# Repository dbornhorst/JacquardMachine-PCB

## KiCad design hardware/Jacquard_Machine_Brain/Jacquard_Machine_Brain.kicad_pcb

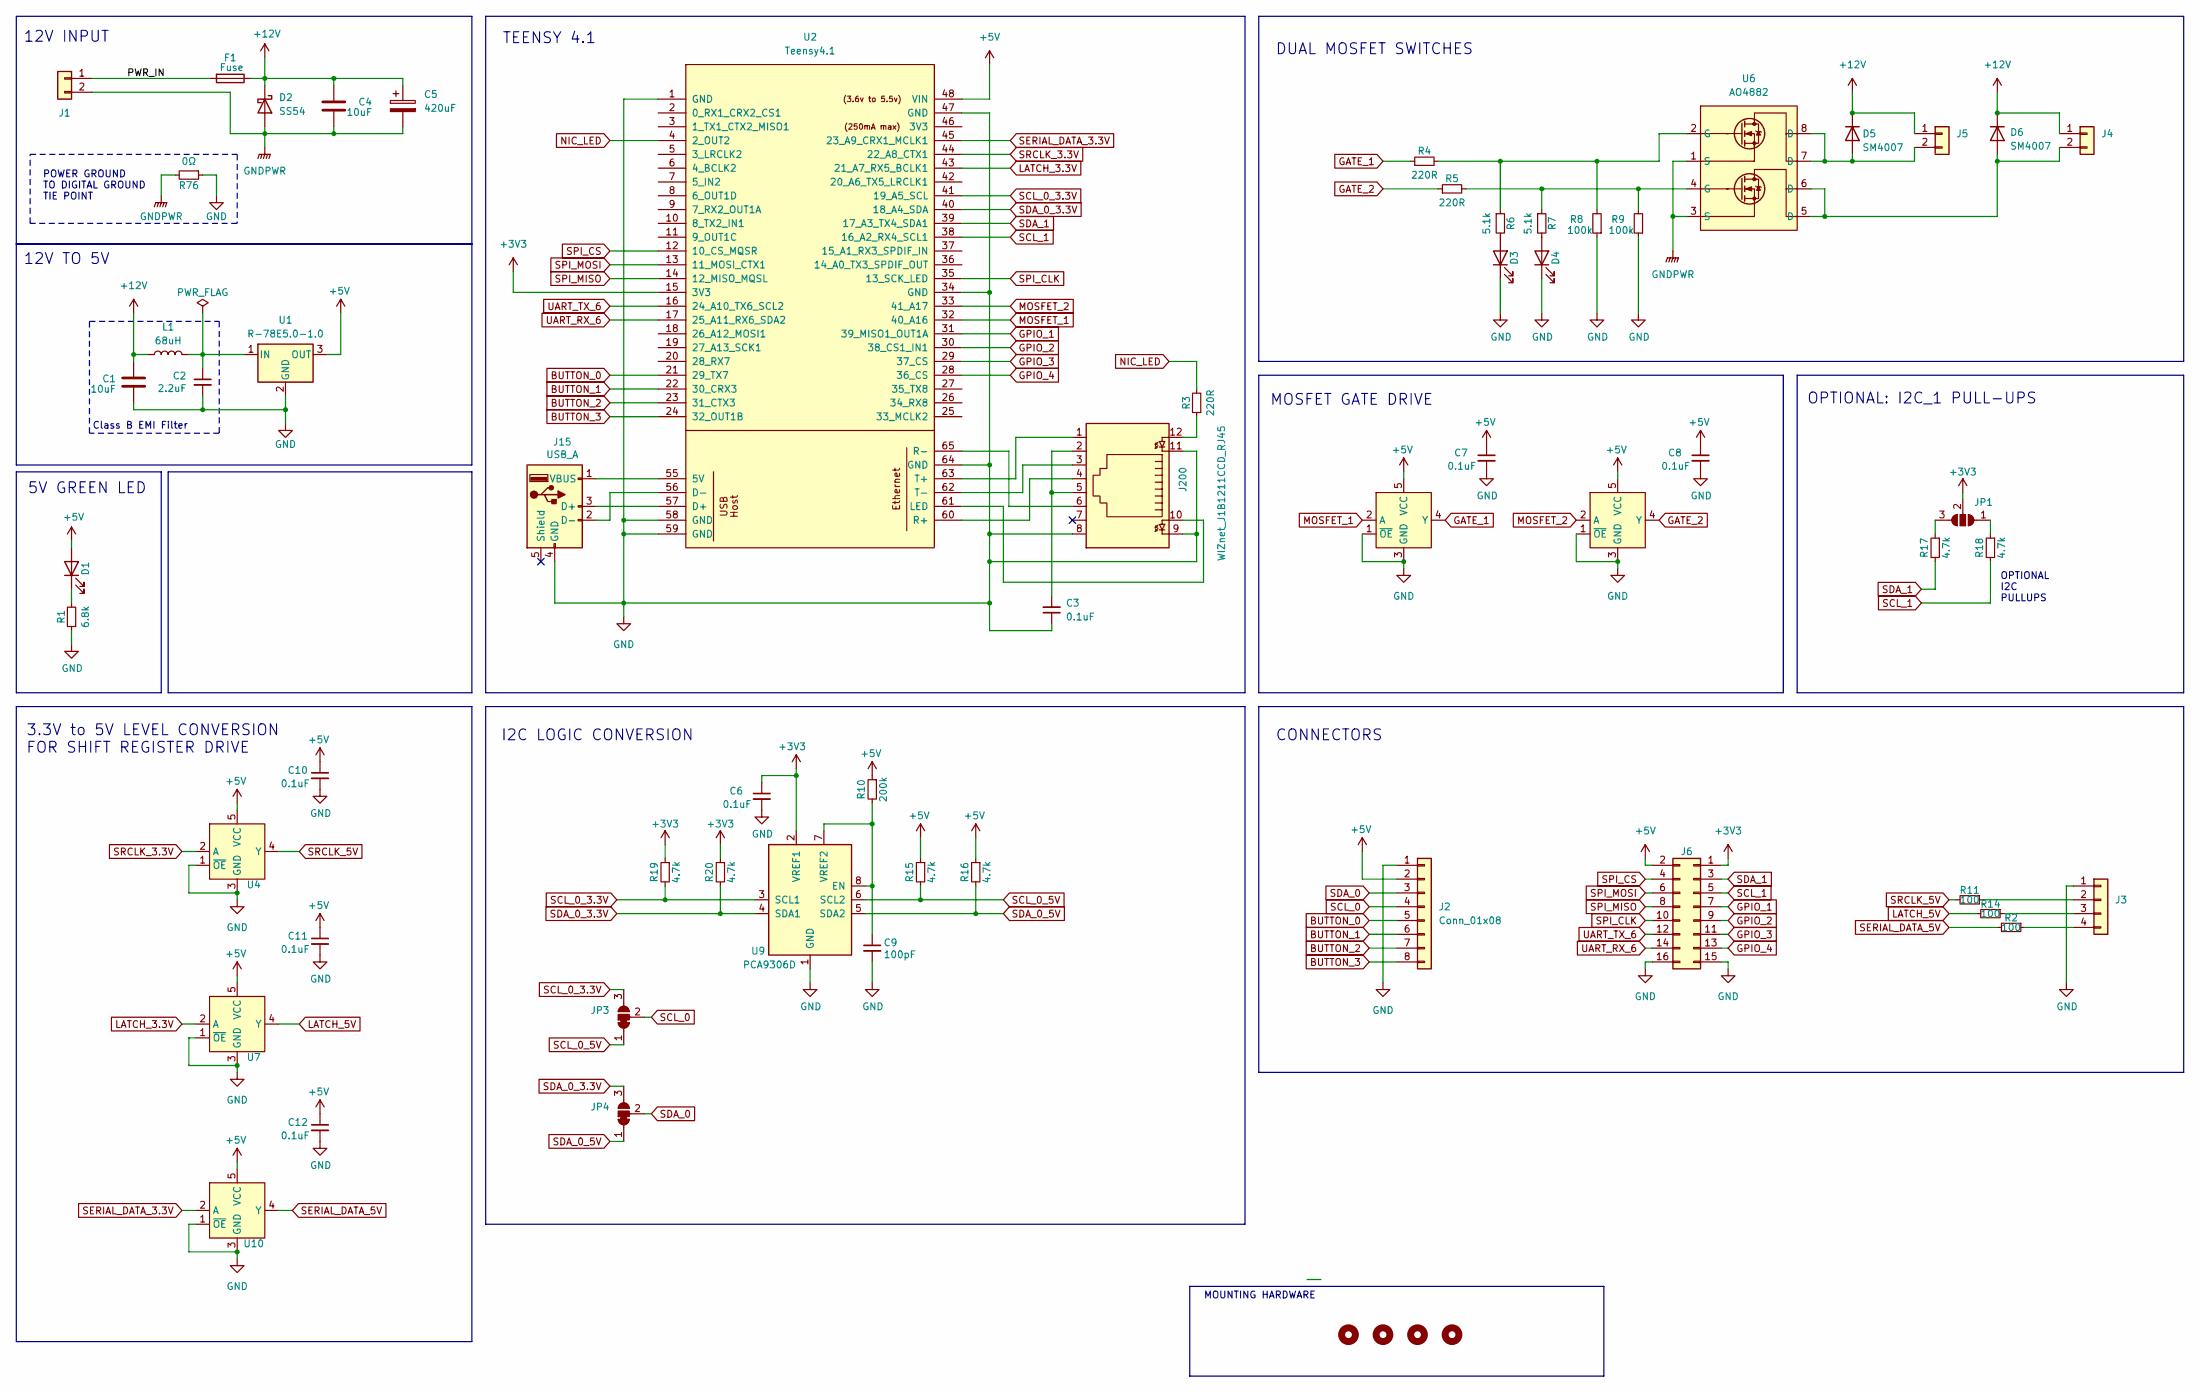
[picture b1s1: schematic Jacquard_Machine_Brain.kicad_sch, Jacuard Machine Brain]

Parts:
C1, C4: 10uF; C_1206_3216Metric; LCSC C13585
C2: 2.2uF; C_0805_2012Metric; LCSC C377773
C3: 0.1uF; C_0805_2012Metric; LCSC C49678
C5: 420uF; CP_Elec_10x7.9; LCSC C3350
C6, C7, C8, C10, C11, C12: 0.1uF; C_0402_1005Metric; LCSC C1525
C9: 100pF; C_0402_1005Metric; LCSC C1546
D1: GREEN LED; LED_0805_2012Metric; LCSC C2297
D2: SS54; D_SMA; LCSC C22452
D3, D4: RED LED; LED_0402_1005Metric; LCSC C397045
D5, D6: SM4007; D_SOD-123; LCSC C64898
F1: Fuse; Fuseholder_2AG_5x15mm_Littelfuse_01110501Z; LCSC C151075
H1, H2, H3, H4: MountingHole; MountingHole_3.2mm_M3_Pad_Via
J1: Terminal Block; TerminalBlock_Phoenix_MKDS-1-2-3.81_1x02_P3.81mm_Horizontal; LCSC C89123
J2: Conn_01x08; PinSocket_1x08_P2.54mm_Vertical; LCSC C42431840
J3: JST-SH 01x04; JST_SH_BM04B-SRSS-TB_1x04-1MP_P1.00mm_Vertical; LCSC C160390
J4, J5: Conn_01x02; PinSocket_1x02_P2.54mm_Vertical; LCSC C7499322
J6: Conn_02x08_Odd_Even; PinSocket_2x08_P2.54mm_Vertical; LCSC C30734
J15: USB_A; SAMTEC_USB-A-S-S-W-TH; LCSC C5815125
J200: WIZnet_J1B1211CCD_RJ45; Digikey P/N 1278-1052-ND
JP1: SolderJumper_3_Bridged123; SolderJumper-3_P1.3mm_Open_RoundedPad1.0x1.5mm
JP3, JP4: SolderJumper_3_Bridged12; SolderJumper-3_P1.3mm_Bridged12_RoundedPad1.0x1.5mm_NumberL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
L1: 68uH; L_Sunlord_SWPA6045S; LCSC C53663
R1: 6.8k; R_0603_1608Metric; LCSC C23212
R2, R11, R14: 100; R_0402_1005Metric; LCSC C25076
R3: 220R; R_0805_2012Metric; Digikey P/N 311-220CRCT-ND
R4, R5: 220R; R_0402_1005Metric; LCSC C25091
R6, R7: 5.1k; R_0402_1005Metric; LCSC C25905
R8, R9: 100k; R_0402_1005Metric; LCSC C25741
R10: 200k; R_0402_1005Metric; LCSC C25764
R15, R16, R17, R18, R19, R20: 4.7k; R_0603_1608Metric; LCSC C23162
R76: 0Ω; R_0805_2012Metric; LCSC C17477
U1: R-78E5.0-1.0; Converter_DCDC_RECOM_R-78E-0.5_THT; LCSC C22371890
U2: Teensy4.1; Teensy41_ethernet_usb; LCSC C41376163
U3, U4, U7, U8, U10: 74AHCT1G125; SOT-353_SC-70-5; LCSC C151417
U6: AO4882; SOIC-8_3.9x4.9mm_P1.27mm; LCSC C477943
U9: PCA9306D; SO-8_3.9x4.9mm_P1.27mm; LCSC C2677369

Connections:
+3V3: C6.1, J6.1, JP1.2 (C), R19.1, R20.1, U2.15 (3V3), U9.2 (VREF1)
+5V: C7.1, C8.1, C10.1, C11.1, C12.1, D1.2 (A), J2.2, J6.2, R10.1, R15.1, R16.1, U1.3 (OUT), U2.48 (VIN), U3.5 (VCC), U4.5 (VCC), U7.5 (VCC), U8.5 (VCC), U10.5 (VCC)
+12V: C1.1, C4.1, C5.1, D2.1 (K), D5.1 (K), D6.1 (K), F1.1, J4.1, J5.1, L1.1
/PWR_IN: F1.2, J1.1
BUTTON_0: J2.5, U2.21 (29_TX7)
BUTTON_1: J2.6, U2.22 (30_CRX3)
BUTTON_2: J2.7, U2.23 (31_CTX3)
BUTTON_3: J2.8, U2.24 (32_OUT1B)
GATE_1: R4.1, U3.4 (Y)
GATE_2: R5.1, U8.4 (Y)
GND: C1.2, C2.2, C3.1, C6.2, C7.2, C8.2, C9.2, C10.2, C11.2, C12.2, D3.1 (K), D4.1 (K), J2.1, J3.1, J6.15, J6.16, J15.4 (GND), J200.8, J200.9, J200.11, R1.1, R8.1, R9.1, R76.1, U1.2 (GND), U2.1 (GND), U2.34 (GND), U2.47 (GND), U2.58 (GND), U2.59 (GND), U2.64 (GND), U3.1 (~OE), U3.3 (GND), U4.1 (~OE), U4.3 (GND), U7.1 (~OE), U7.3 (GND), U8.1 (~OE), U8.3 (GND), U9.1 (GND), U10.1 (~OE), U10.3 (GND)
GNDPWR: C4.2, C5.2, D2.2 (A), J1.2, R76.2, U6.1 (S), U6.3 (S)
GPIO_1: J6.7, U2.31 (39_MISO1_OUT1A)
GPIO_2: J6.9, U2.30 (38_CS1_IN1)
GPIO_3: J6.11, U2.29 (37_CS)
GPIO_4: J6.13, U2.28 (36_CS)
LATCH_3.3V: U2.43 (21_A7_RX5_BCLK1), U7.2 (A)
LATCH_5V: R14.2, U7.4 (Y)
MOSFET_1: U2.32 (40_A16), U3.2 (A)
MOSFET_2: U2.33 (41_A17), U8.2 (A)
NIC_LED: R3.2, U2.4 (2_OUT2)
unnamed: C3.2, J200.2, J200.5
unnamed: D1.1 (K), R1.2
unnamed: D3.2 (A), R6.2
unnamed: D4.2 (A), R7.2
unnamed: D5.2 (A), J5.2, U6.7 (D), U6.8 (D)
unnamed: D6.2 (A), J4.2, U6.5 (D), U6.6 (D)
unnamed: J3.2, R11.1
unnamed: J3.3, R14.1
unnamed: J3.4, R2.1
unnamed: J15.3 (D+), U2.57 (D+)
unnamed: J15.2 (D-), U2.56 (D-)
unnamed: J15.1 (VBUS), U2.55 (5V)
unnamed: J200.12, R3.1
unnamed: JP1.1 (A), R18.1
unnamed: JP1.3 (B), R17.1
unnamed: R4.2, R6.1, R8.2, U6.2 (G)
unnamed: R5.2, R7.1, R9.2, U6.4 (G)
unnamed: C2.1, L1.2, U1.1 (IN)
unnamed: J200.10, U2.61 (LED)
unnamed: J200.4, U2.60 (R+)
unnamed: J200.6, U2.65 (R-)
unnamed: J200.1, U2.63 (T+)
unnamed: J200.3, U2.62 (T-)
unnamed: C9.1, R10.2, U9.7 (VREF2), U9.8 (EN)
SCL_0: J2.4, JP3.2 (C)
SCL_0_3.3V: JP3.3 (B), R19.2, U2.41 (19_A5_SCL), U9.3 (SCL1)
SCL_0_5V: JP3.1 (A), R15.2, U9.6 (SCL2)
SCL_1: J6.5, R18.2, U2.38 (16_A2_RX4_SCL1)
SDA_0: J2.3, JP4.2 (C)
SDA_0_3.3V: JP4.3 (B), R20.2, U2.40 (18_A4_SDA), U9.4 (SDA1)
SDA_0_5V: JP4.1 (A), R16.2, U9.5 (SDA2)
SDA_1: J6.3, R17.2, U2.39 (17_A3_TX4_SDA1)
SERIAL_DATA_3.3V: U2.45 (23_A9_CRX1_MCLK1), U10.2 (A)
SERIAL_DATA_5V: R2.2, U10.4 (Y)
SPI_CLK: J6.10, U2.35 (13_SCK_LED)
SPI_CS: J6.4, U2.12 (10_CS_MQSR)
SPI_MISO: J6.8, U2.14 (12_MISO_MQSL)
SPI_MOSI: J6.6, U2.13 (11_MOSI_CTX1)
SRCLK_3.3V: U2.44 (22_A8_CTX1), U4.2 (A)
SRCLK_5V: R11.2, U4.4 (Y)
UART_RX_6: J6.14, U2.17 (25_A11_RX6_SDA2)
UART_TX_6: J6.12, U2.16 (24_A10_TX6_SCL2)

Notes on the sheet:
OPTIONAL: I2C_1 PULL-UPS
5V GREEN LED
3.3V to 5V LEVEL CONVERSION FOR SHIFT REGISTER DRIVE
I2C LOGIC CONVERSION
TEENSY 4.1
MOSFET GATE DRIVE
DUAL MOSFET SWITCHES
MOUNTING HARDWARE
OPTIONAL I2C PULLUPS
12V INPUT
12V TO 5V
Class B EMI Filter
POWER GROUND TO DIGITAL GROUND TIE POINT
CONNECTORS

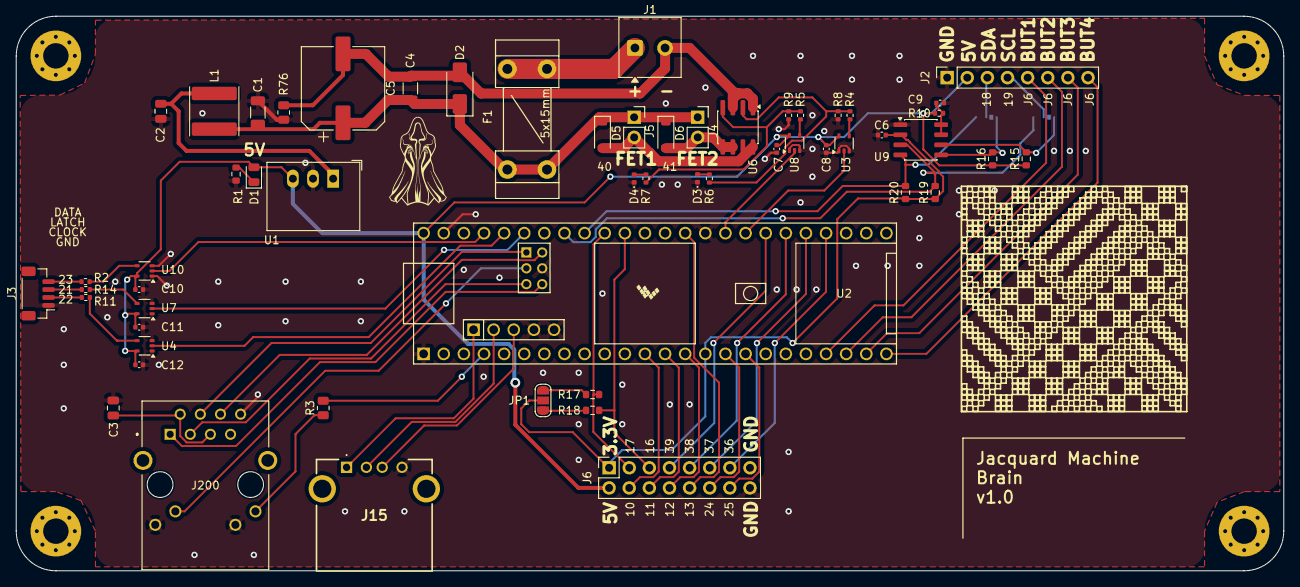
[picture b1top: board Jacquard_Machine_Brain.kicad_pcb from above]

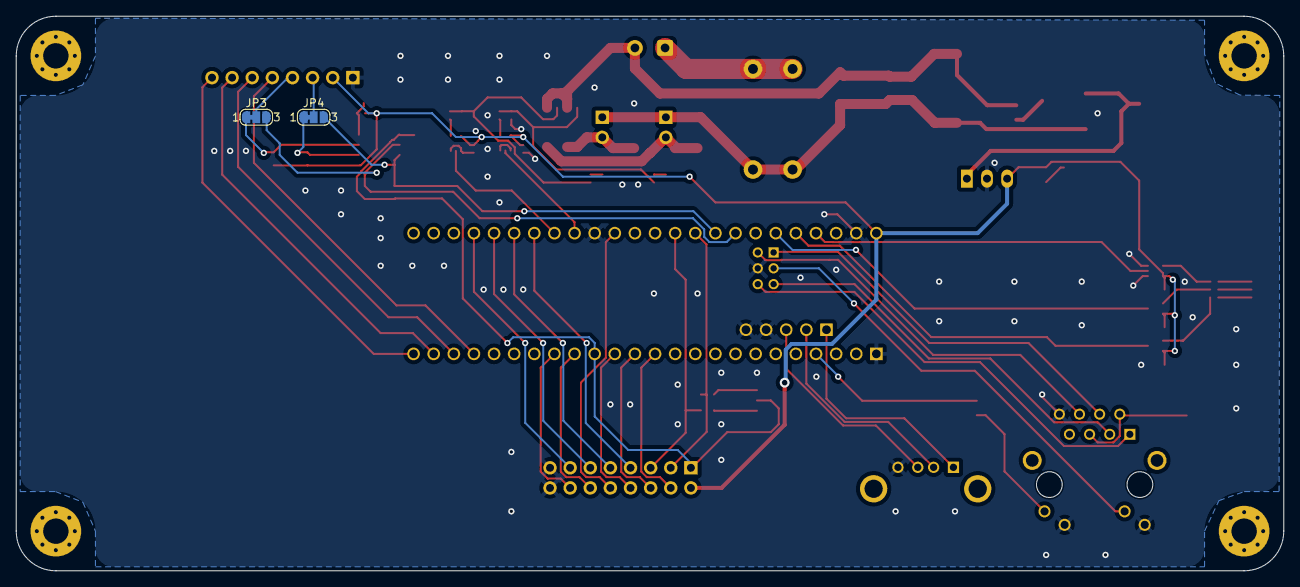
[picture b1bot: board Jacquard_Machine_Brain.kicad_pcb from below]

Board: 2 copper layers, 160.0 x 70.0 mm, 63 parts (2 on the bottom side), 63 nets.

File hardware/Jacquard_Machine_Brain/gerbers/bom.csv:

Designator,Footprint,Quantity,Value,LCSC Part #
"C1, C4",1206,2,10uF,C13585
"C10, C11, C12, C6, C7, C8",0402,6,0.1uF,C1525
C2,0805,1,2.2uF,C50254
C3,0805,1,0.1uF,C49678
C5,CP_Elec_10x7.9,1,420uF,C3350
C9,0402,1,100pF,C1546
D1,0805,1,GREEN LED,C2297
D2,D_SMA,1,SS54,C22452
"D3, D4",0402,2,RED LED,C397045
"D5, D6",D_SOD-123,2,SM4007,C64898
F1,Fuseholder_2AG_5x15mm_Littelfuse_01110501Z,1,Fuse,C151075
J1,TerminalBlock_Phoenix_MKDS-1-2-3.81_1x02_P3.81mm_Horizontal,1,Terminal Block,C89123
J15,SAMTEC_USB-A-S-S-W-TH,1,USB_A,C5815125
J2,PinSocket_1x08_P2.54mm_Vertical,1,Conn_01x08,C42431840
J200,WIZnet_J1B1211CCD_RJ45,1,WIZnet_J1B1211CCD_RJ45,C910371
J3,JST_SH_BM04B-SRSS-TB_1x04-1MP_P1.00mm_Vertical,1,JST-SH 01x04,C160390
"J4, J5",PinSocket_1x02_P2.54mm_Vertical,2,Conn_01x02,C7499322
J6,PinSocket_2x08_P2.54mm_Vertical,1,Conn_02x08_Odd_Even,C30734
L1,L_Sunlord_SWPA6045S,1,68uH,C53663
R1,0603,1,6.8k,C23212
R10,0402,1,200k,C25764
"R11, R14, R2",0402,3,100,C25076
"R15, R16, R17, R18, R19, R20",0603,6,4.7k,C23162
R3,0805,1,220R,C17557
"R4, R5",0402,2,220R,C25091
"R6, R7",0402,2,5.1k,C25905
R76,0805,1,0Ω,C17477
"R8, R9",0402,2,100k,C25741
U1,Converter_DCDC_RECOM_R-78E-0.5_THT,1,R-78E5.0-1.0,C22371890
"U10, U3, U4, U7, U8",SOT-353_SC-70-5,5,74AHCT1G125,C151417
U2,Teensy41_ethernet_usb,1,Teensy4.1,C41376163
U6,SOIC-8_3.9x4.9mm_P1.27mm,1,AO4882,C477943
U9,SO-8_3.9x4.9mm_P1.27mm,1,PCA9306D,C2677369

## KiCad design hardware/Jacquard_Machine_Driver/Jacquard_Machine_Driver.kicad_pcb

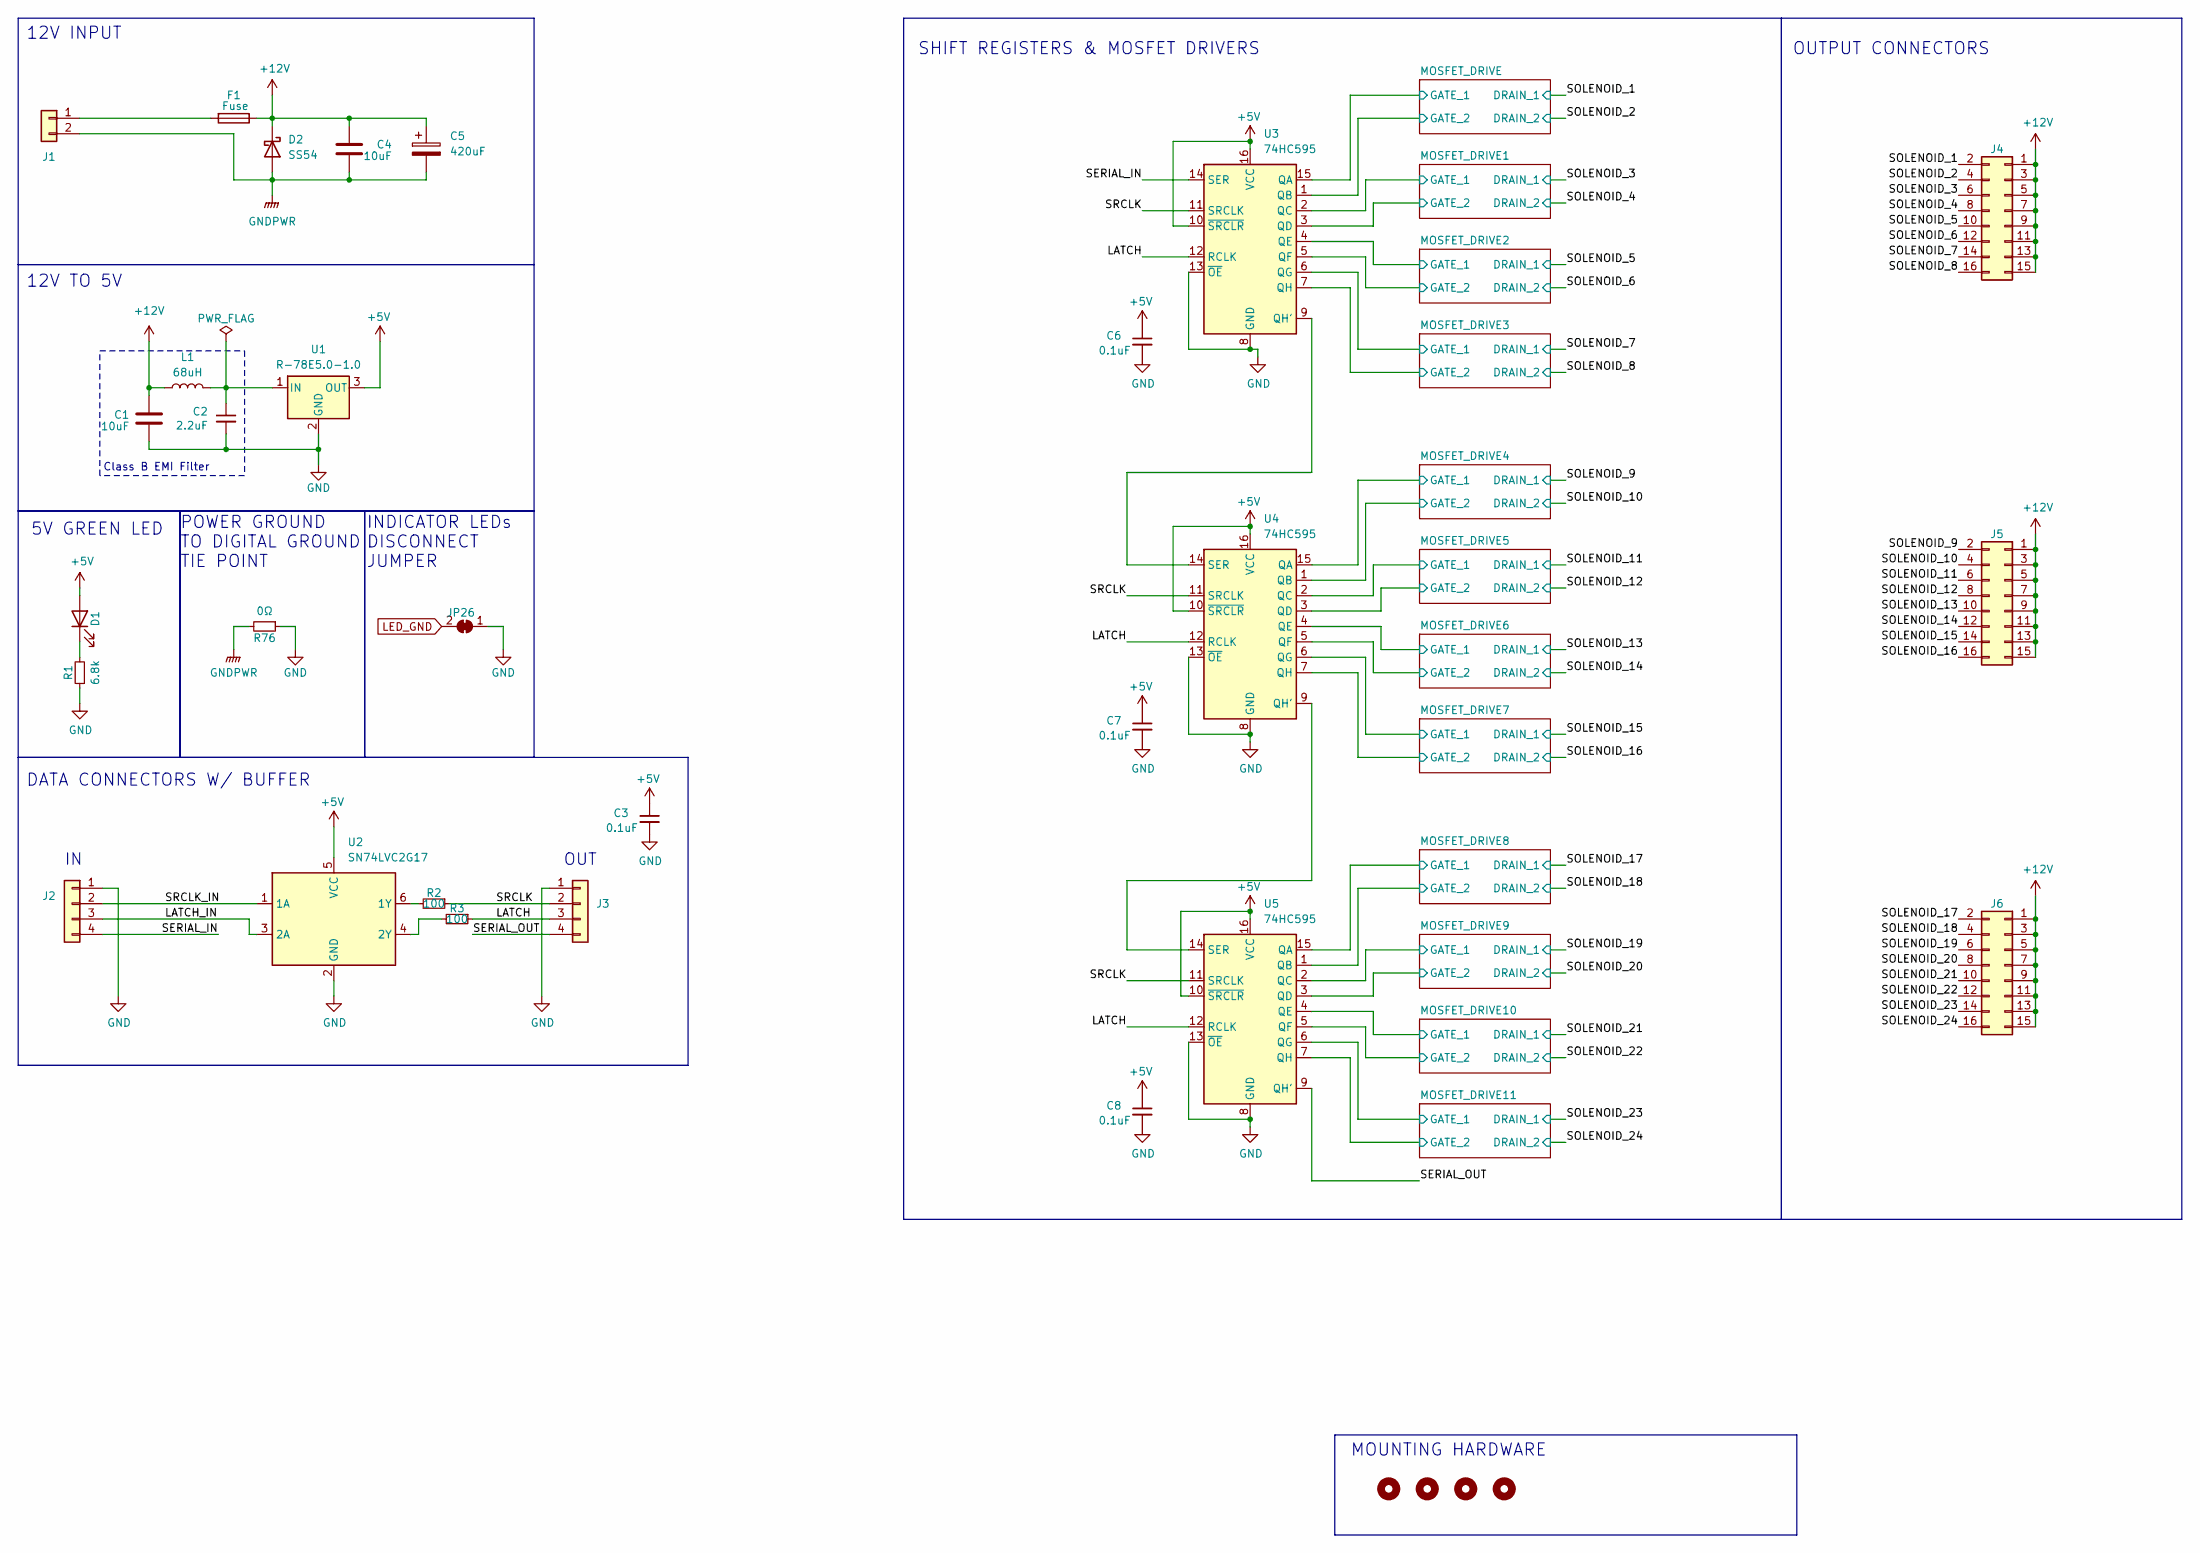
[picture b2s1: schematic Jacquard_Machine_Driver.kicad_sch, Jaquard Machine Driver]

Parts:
C1, C4: 10uF; C_1206_3216Metric; LCSC C13585
C2: 2.2uF; C_0805_2012Metric; LCSC C377773
C3, C6, C7, C8: 0.1uF; C_0402_1005Metric; LCSC C1525
C5: 420uF; CP_Elec_10x7.9; LCSC C3350
D1: GREEN LED; LED_0805_2012Metric; LCSC C2297
D2: SS54; D_SMA; LCSC C22452
F1: Fuse; Fuseholder_2AG_5x15mm_Littelfuse_01110501Z; LCSC C151075
H1, H2, H3, H4: MountingHole; MountingHole_3.2mm_M3_Pad_Via
J1: Terminal Block; TerminalBlock_Phoenix_MKDS-1-2-3.81_1x02_P3.81mm_Horizontal; LCSC C89123
J2, J3: JST-SH 01x04; JST_SH_BM04B-SRSS-TB_1x04-1MP_P1.00mm_Vertical; LCSC C160390
J4, J5, J6: Conn_02x08_Odd_Even; PinSocket_2x08_P2.54mm_Vertical; LCSC C30734
JP26: SolderJumper_2_Bridged; SolderJumper-2_P1.3mm_Bridged_RoundedPad1.0x1.5mm
L1: 68uH; L_Sunlord_SWPA6045S; LCSC C53663
R1: 6.8k; R_0603_1608Metric; LCSC C23212
R2, R3: 100; R_0402_1005Metric; LCSC C25076
R76: 0Ω; R_0805_2012Metric; LCSC C17477
U1: R-78E5.0-1.0; Converter_DCDC_RECOM_R-78E-0.5_THT; LCSC C22371890
U2: SN74LVC2G17; SOT-23-6_Handsoldering; LCSC C10429
U3, U4, U5: 74HC595; TSSOP-16_4.4x5mm_P0.65mm; LCSC C273642

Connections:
+5V: C3.1, C6.1, C7.1, C8.1, D1.2 (A), U1.3 (OUT), U2.5 (VCC), U3.10 (~SRCLR), U3.16 (VCC), U4.10 (~SRCLR), U4.16 (VCC), U5.10 (~SRCLR), U5.16 (VCC)
+12V: C1.1, C4.1, C5.1, D2.1 (K), F1.1, J4.1, J4.3, J4.5, J4.7, J4.9, J4.11, J4.13, J4.15, J5.1, J5.3, J5.5, J5.7, J5.9, J5.11, J5.13, J5.15, J6.1, J6.3, J6.5, J6.7, J6.9, J6.11, J6.13, J6.15, L1.1; also elsewhere on the board
/LATCH: J3.3, R3.1, U3.12 (RCLK), U4.12 (RCLK), U5.12 (RCLK)
/MOSFET_DRIVE1/GATE_1: U3.2 (QC); also elsewhere on the board
/MOSFET_DRIVE1/GATE_2: U3.3 (QD); also elsewhere on the board
/MOSFET_DRIVE2/GATE_1: U3.4 (QE); also elsewhere on the board
/MOSFET_DRIVE2/GATE_2: U3.5 (QF); also elsewhere on the board
/MOSFET_DRIVE3/GATE_1: U3.6 (QG); also elsewhere on the board
/MOSFET_DRIVE3/GATE_2: U3.7 (QH); also elsewhere on the board
/MOSFET_DRIVE4/GATE_1: U4.15 (QA); also elsewhere on the board
/MOSFET_DRIVE4/GATE_2: U4.1 (QB); also elsewhere on the board
/MOSFET_DRIVE5/GATE_1: U4.2 (QC); also elsewhere on the board
/MOSFET_DRIVE5/GATE_2: U4.3 (QD); also elsewhere on the board
/MOSFET_DRIVE6/GATE_1: U4.4 (QE); also elsewhere on the board
/MOSFET_DRIVE6/GATE_2: U4.5 (QF); also elsewhere on the board
/MOSFET_DRIVE7/GATE_1: U4.6 (QG); also elsewhere on the board
/MOSFET_DRIVE7/GATE_2: U4.7 (QH); also elsewhere on the board
/MOSFET_DRIVE8/GATE_1: U5.15 (QA); also elsewhere on the board
/MOSFET_DRIVE8/GATE_2: U5.1 (QB); also elsewhere on the board
/MOSFET_DRIVE9/GATE_1: U5.2 (QC); also elsewhere on the board
/MOSFET_DRIVE9/GATE_2: U5.3 (QD); also elsewhere on the board
/MOSFET_DRIVE10/GATE_1: U5.4 (QE); also elsewhere on the board
/MOSFET_DRIVE10/GATE_2: U5.5 (QF); also elsewhere on the board
/MOSFET_DRIVE11/GATE_1: U5.6 (QG); also elsewhere on the board
/MOSFET_DRIVE11/GATE_2: U5.7 (QH); also elsewhere on the board
/MOSFET_DRIVE/GATE_1: U3.15 (QA); also elsewhere on the board
/MOSFET_DRIVE/GATE_2: U3.1 (QB); also elsewhere on the board
/SERIAL_IN: J2.4, U3.14 (SER)
/SERIAL_OUT: J3.4, U5.9 (QH')
/SOLENOID_1: J4.2; also elsewhere on the board
/SOLENOID_2: J4.4; also elsewhere on the board
/SOLENOID_3: J4.6; also elsewhere on the board
/SOLENOID_4: J4.8; also elsewhere on the board
/SOLENOID_5: J4.10; also elsewhere on the board
/SOLENOID_6: J4.12; also elsewhere on the board
/SOLENOID_7: J4.14; also elsewhere on the board
/SOLENOID_8: J4.16; also elsewhere on the board
/SOLENOID_9: J5.2; also elsewhere on the board
/SOLENOID_10: J5.4; also elsewhere on the board
/SOLENOID_11: J5.6; also elsewhere on the board
/SOLENOID_12: J5.8; also elsewhere on the board
/SOLENOID_13: J5.10; also elsewhere on the board
/SOLENOID_14: J5.12; also elsewhere on the board
/SOLENOID_15: J5.14; also elsewhere on the board
/SOLENOID_16: J5.16; also elsewhere on the board
/SOLENOID_17: J6.2; also elsewhere on the board
/SOLENOID_18: J6.4; also elsewhere on the board
/SOLENOID_19: J6.6; also elsewhere on the board
/SOLENOID_20: J6.8; also elsewhere on the board
/SOLENOID_21: J6.10; also elsewhere on the board
/SOLENOID_22: J6.12; also elsewhere on the board
/SOLENOID_23: J6.14; also elsewhere on the board
/SOLENOID_24: J6.16; also elsewhere on the board
/SRCLK: J3.2, R2.1, U3.11 (SRCLK), U4.11 (SRCLK), U5.11 (SRCLK)
GND: C1.2, C2.2, C3.2, C6.2, C7.2, C8.2, J2.1, J3.1, JP26.1 (A), R1.1, R76.1, U1.2 (GND), U2.2 (GND), U3.8 (GND), U3.13 (~OE), U4.8 (GND), U4.13 (~OE), U5.8 (GND), U5.13 (~OE); also elsewhere on the board
GNDPWR: C4.2, C5.2, D2.2 (A), J1.2, R76.2; also elsewhere on the board
LED_GND: JP26.2 (B); also elsewhere on the board
unnamed: D1.1 (K), R1.2
unnamed: F1.2, J1.1
unnamed: J2.2, U2.1 (1A)
unnamed: J2.3, U2.3 (2A)
unnamed: C2.1, L1.2, U1.1 (IN)
unnamed: R2.2, U2.6 (1Y)
unnamed: R3.2, U2.4 (2Y)
unnamed: U3.9 (QH'), U4.14 (SER)
unnamed: U4.9 (QH'), U5.14 (SER)

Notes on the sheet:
POWER GROUND TO DIGITAL GROUND TIE POINT
DATA CONNECTORS W/ BUFFER
OUT
INDICATOR LEDs DISCONNECT JUMPER
5V GREEN LED
Class B EMI Filter
OUTPUT CONNECTORS
MOUNTING HARDWARE
12V TO 5V
SHIFT REGISTERS & MOSFET DRIVERS
12V INPUT

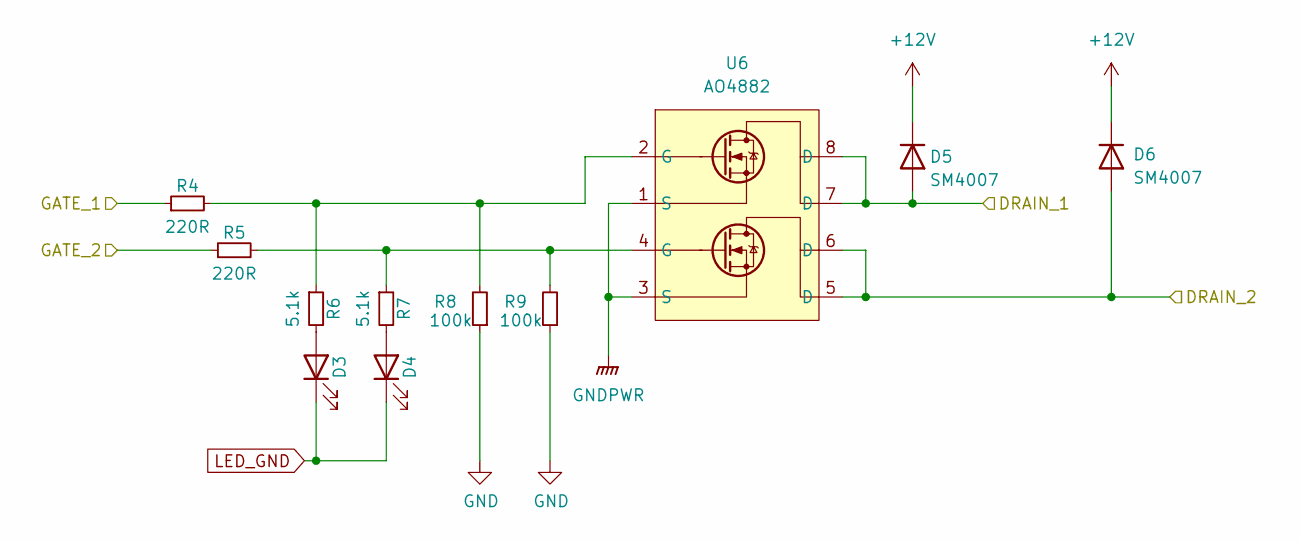
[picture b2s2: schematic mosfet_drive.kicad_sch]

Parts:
D3, D4: RED LED; LED_0402_1005Metric; LCSC C397045
D5, D6: SM4007; D_SOD-123; LCSC C64898
R4, R5: 220R; R_0402_1005Metric; LCSC C25091
R6, R7: 5.1k; R_0402_1005Metric; LCSC C25905
R8, R9: 100k; R_0402_1005Metric; LCSC C25741
U6: AO4882; SOIC-8_3.9x4.9mm_P1.27mm; LCSC C477943

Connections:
+12V: D5.1 (K), D6.1 (K); also elsewhere on the board
/MOSFET_DRIVE/GATE_1: R4.1; also elsewhere on the board
/MOSFET_DRIVE/GATE_2: R5.1; also elsewhere on the board
/SOLENOID_1: D5.2 (A), U6.7 (D), U6.8 (D); also elsewhere on the board
/SOLENOID_2: D6.2 (A), U6.5 (D), U6.6 (D); also elsewhere on the board
GND: R8.1, R9.1; also elsewhere on the board
GNDPWR: U6.1 (S), U6.3 (S); also elsewhere on the board
LED_GND: D3.1 (K), D4.1 (K); also elsewhere on the board
unnamed: D3.2 (A), R6.2
unnamed: D4.2 (A), R7.2
unnamed: R4.2, R6.1, R8.2, U6.2 (G)
unnamed: R5.2, R7.1, R9.2, U6.4 (G)

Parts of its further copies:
D7, D8, D11, D12, D15, D16, D19, D20, D23, D24, D27, D28, D31, D32, D35, D36, D39, D40, D43, D44, D47, D48: RED LED; LED_0402_1005Metric; LCSC C397045
D9, D10, D13, D14, D17, D18, D21, D22, D25, D26, D29, D30, D33, D34, D37, D38, D41, D42, D45, D46, D49, D50: SM4007; D_SOD-123; LCSC C64898
R10, R11, R16, R17, R22, R23, R28, R29, R34, R35, R40, R41, R46, R47, R52, R53, R58, R59, R64, R65, R70, R71: 220R; R_0402_1005Metric; LCSC C25091
R12, R13, R18, R19, R24, R25, R30, R31, R36, R37, R42, R43, R48, R49, R54, R55, R60, R61, R66, R67, R72, R73: 5.1k; R_0402_1005Metric; LCSC C25905
R14, R15, R20, R21, R26, R27, R32, R33, R38, R39, R44, R45, R50, R51, R56, R57, R62, R63, R68, R69, R74, R75: 100k; R_0402_1005Metric; LCSC C25741
U7, U8, U9, U10, U11, U12, U13, U14, U15, U16, U17: AO4882; SOIC-8_3.9x4.9mm_P1.27mm; LCSC C477943

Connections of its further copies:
+12V: D9.1 (K), D10.1 (K), D13.1 (K), D14.1 (K), D17.1 (K), D18.1 (K), D21.1 (K), D22.1 (K), D25.1 (K), D26.1 (K), D29.1 (K), D30.1 (K), D33.1 (K), D34.1 (K), D37.1 (K), D38.1 (K), D41.1 (K), D42.1 (K), D45.1 (K), D46.1 (K), D49.1 (K), D50.1 (K); also elsewhere on the board
/MOSFET_DRIVE1/GATE_1: R10.1; also elsewhere on the board
/MOSFET_DRIVE1/GATE_2: R11.1; also elsewhere on the board
/MOSFET_DRIVE2/GATE_1: R16.1; also elsewhere on the board
/MOSFET_DRIVE2/GATE_2: R17.1; also elsewhere on the board
/MOSFET_DRIVE3/GATE_1: R22.1; also elsewhere on the board
/MOSFET_DRIVE3/GATE_2: R23.1; also elsewhere on the board
/MOSFET_DRIVE4/GATE_1: R28.1; also elsewhere on the board
/MOSFET_DRIVE4/GATE_2: R29.1; also elsewhere on the board
/MOSFET_DRIVE5/GATE_1: R34.1; also elsewhere on the board
/MOSFET_DRIVE5/GATE_2: R35.1; also elsewhere on the board
/MOSFET_DRIVE6/GATE_1: R40.1; also elsewhere on the board
/MOSFET_DRIVE6/GATE_2: R41.1; also elsewhere on the board
/MOSFET_DRIVE7/GATE_1: R46.1; also elsewhere on the board
/MOSFET_DRIVE7/GATE_2: R47.1; also elsewhere on the board
/MOSFET_DRIVE8/GATE_1: R52.1; also elsewhere on the board
/MOSFET_DRIVE8/GATE_2: R53.1; also elsewhere on the board
/MOSFET_DRIVE9/GATE_1: R58.1; also elsewhere on the board
/MOSFET_DRIVE9/GATE_2: R59.1; also elsewhere on the board
/MOSFET_DRIVE10/GATE_1: R64.1; also elsewhere on the board
/MOSFET_DRIVE10/GATE_2: R65.1; also elsewhere on the board
/MOSFET_DRIVE11/GATE_1: R70.1; also elsewhere on the board
/MOSFET_DRIVE11/GATE_2: R71.1; also elsewhere on the board
/SOLENOID_3: D9.2 (A), U7.7 (D), U7.8 (D); also elsewhere on the board
/SOLENOID_4: D10.2 (A), U7.5 (D), U7.6 (D); also elsewhere on the board
/SOLENOID_5: D13.2 (A), U8.7 (D), U8.8 (D); also elsewhere on the board
/SOLENOID_6: D14.2 (A), U8.5 (D), U8.6 (D); also elsewhere on the board
/SOLENOID_7: D17.2 (A), U9.7 (D), U9.8 (D); also elsewhere on the board
/SOLENOID_8: D18.2 (A), U9.5 (D), U9.6 (D); also elsewhere on the board
/SOLENOID_9: D21.2 (A), U10.7 (D), U10.8 (D); also elsewhere on the board
/SOLENOID_10: D22.2 (A), U10.5 (D), U10.6 (D); also elsewhere on the board
/SOLENOID_11: D25.2 (A), U11.7 (D), U11.8 (D); also elsewhere on the board
/SOLENOID_12: D26.2 (A), U11.5 (D), U11.6 (D); also elsewhere on the board
/SOLENOID_13: D29.2 (A), U12.7 (D), U12.8 (D); also elsewhere on the board
/SOLENOID_14: D30.2 (A), U12.5 (D), U12.6 (D); also elsewhere on the board
/SOLENOID_15: D33.2 (A), U13.7 (D), U13.8 (D); also elsewhere on the board
/SOLENOID_16: D34.2 (A), U13.5 (D), U13.6 (D); also elsewhere on the board
/SOLENOID_17: D37.2 (A), U14.7 (D), U14.8 (D); also elsewhere on the board
/SOLENOID_18: D38.2 (A), U14.5 (D), U14.6 (D); also elsewhere on the board
/SOLENOID_19: D41.2 (A), U15.7 (D), U15.8 (D); also elsewhere on the board
/SOLENOID_20: D42.2 (A), U15.5 (D), U15.6 (D); also elsewhere on the board
/SOLENOID_21: D45.2 (A), U16.7 (D), U16.8 (D); also elsewhere on the board
/SOLENOID_22: D46.2 (A), U16.5 (D), U16.6 (D); also elsewhere on the board
/SOLENOID_23: D49.2 (A), U17.7 (D), U17.8 (D); also elsewhere on the board
/SOLENOID_24: D50.2 (A), U17.5 (D), U17.6 (D); also elsewhere on the board
GND: R14.1, R15.1, R20.1, R21.1, R26.1, R27.1, R32.1, R33.1, R38.1, R39.1, R44.1, R45.1, R50.1, R51.1, R56.1, R57.1, R62.1, R63.1, R68.1, R69.1, R74.1, R75.1; also elsewhere on the board
GNDPWR: U7.1 (S), U7.3 (S), U8.1 (S), U8.3 (S), U9.1 (S), U9.3 (S), U10.1 (S), U10.3 (S), U11.1 (S), U11.3 (S), U12.1 (S), U12.3 (S), U13.1 (S), U13.3 (S), U14.1 (S), U14.3 (S), U15.1 (S), U15.3 (S), U16.1 (S), U16.3 (S), U17.1 (S), U17.3 (S); also elsewhere on the board
LED_GND: D7.1 (K), D8.1 (K), D11.1 (K), D12.1 (K), D15.1 (K), D16.1 (K), D19.1 (K), D20.1 (K), D23.1 (K), D24.1 (K), D27.1 (K), D28.1 (K), D31.1 (K), D32.1 (K), D35.1 (K), D36.1 (K), D39.1 (K), D40.1 (K), D43.1 (K), D44.1 (K), D47.1 (K), D48.1 (K); also elsewhere on the board
unnamed: D7.2 (A), R12.2
unnamed: D8.2 (A), R13.2
unnamed: D11.2 (A), R18.2
unnamed: D12.2 (A), R19.2
unnamed: D15.2 (A), R24.2
unnamed: D16.2 (A), R25.2
unnamed: D19.2 (A), R30.2
unnamed: D20.2 (A), R31.2
unnamed: D23.2 (A), R36.2
unnamed: D24.2 (A), R37.2
unnamed: D27.2 (A), R42.2
unnamed: D28.2 (A), R43.2
unnamed: D31.2 (A), R48.2
unnamed: D32.2 (A), R49.2
unnamed: D35.2 (A), R54.2
unnamed: D36.2 (A), R55.2
unnamed: D39.2 (A), R60.2
unnamed: D40.2 (A), R61.2
unnamed: D43.2 (A), R66.2
unnamed: D44.2 (A), R67.2
unnamed: D47.2 (A), R72.2
unnamed: D48.2 (A), R73.2
unnamed: R10.2, R12.1, R14.2, U7.2 (G)
unnamed: R11.2, R13.1, R15.2, U7.4 (G)
unnamed: R16.2, R18.1, R20.2, U8.2 (G)
unnamed: R17.2, R19.1, R21.2, U8.4 (G)
unnamed: R22.2, R24.1, R26.2, U9.2 (G)
unnamed: R23.2, R25.1, R27.2, U9.4 (G)
unnamed: R28.2, R30.1, R32.2, U10.2 (G)
unnamed: R29.2, R31.1, R33.2, U10.4 (G)
unnamed: R34.2, R36.1, R38.2, U11.2 (G)
unnamed: R35.2, R37.1, R39.2, U11.4 (G)
unnamed: R40.2, R42.1, R44.2, U12.2 (G)
unnamed: R41.2, R43.1, R45.2, U12.4 (G)
unnamed: R46.2, R48.1, R50.2, U13.2 (G)
unnamed: R47.2, R49.1, R51.2, U13.4 (G)
unnamed: R52.2, R54.1, R56.2, U14.2 (G)
unnamed: R53.2, R55.1, R57.2, U14.4 (G)
unnamed: R58.2, R60.1, R62.2, U15.2 (G)
unnamed: R59.2, R61.1, R63.2, U15.4 (G)
unnamed: R64.2, R66.1, R68.2, U16.2 (G)
unnamed: R65.2, R67.1, R69.2, U16.4 (G)
unnamed: R70.2, R72.1, R74.2, U17.2 (G)
unnamed: R71.2, R73.1, R75.2, U17.4 (G)

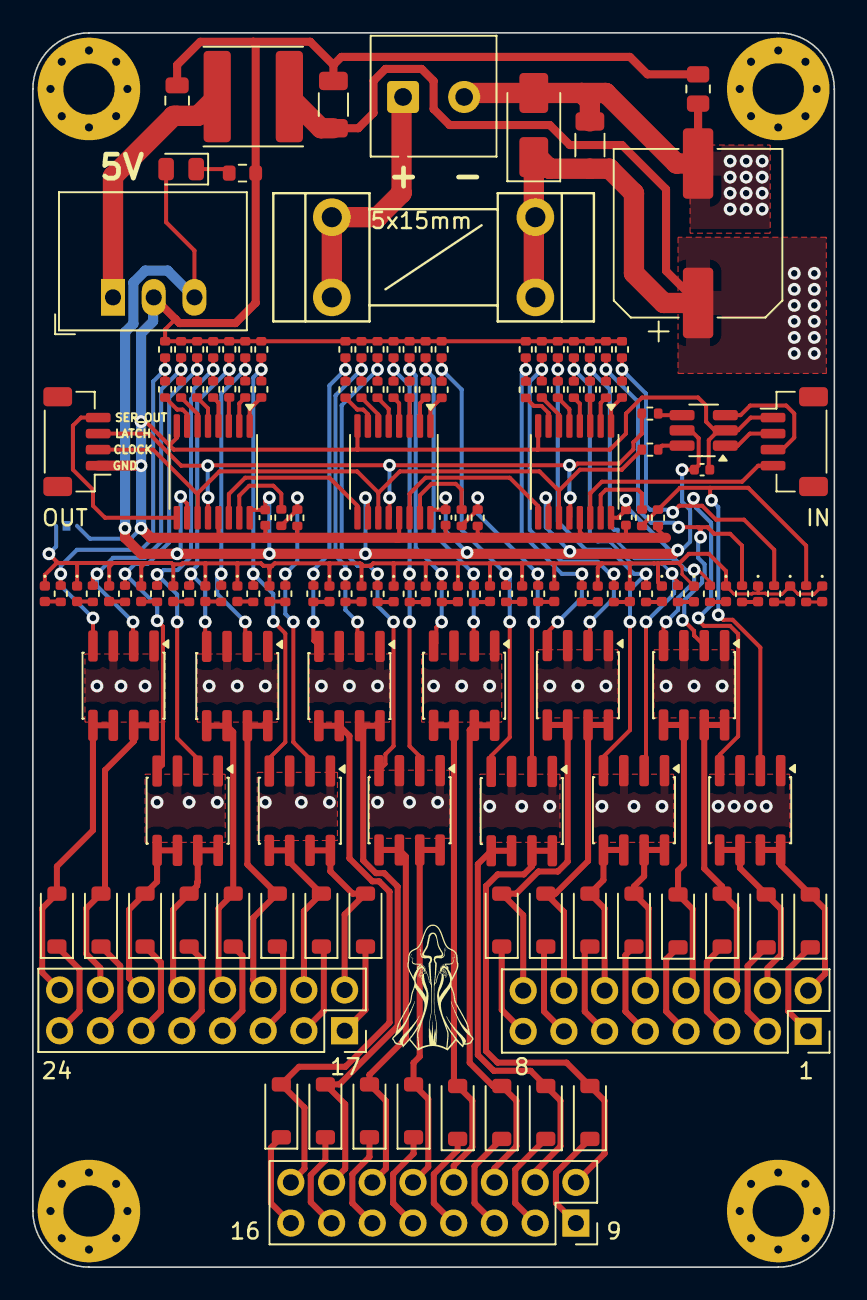
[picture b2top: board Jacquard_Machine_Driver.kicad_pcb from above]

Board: 2 copper layers, 50.0 x 77.0 mm, 164 parts (1 on the bottom side), 114 nets.

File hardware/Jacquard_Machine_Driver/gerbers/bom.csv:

Designator,Footprint,Quantity,Value,LCSC Part #
"C1, C4",1206,2,10uF,C13585
C2,0805,1,2.2uF,C377773
"C3, C6, C7, C8",0402,4,0.1uF,C1525
C5,CP_Elec_10x7.9,1,420uF,C3350
D1,0805,1,GREEN LED,C2297
"D10, D13, D14, D17, D18, D21, D22, D25, D26, D29, D30, D33, D34, D37, D38, D41, D42, D45, D46, D49, D5, D50, D6, D9",D_SOD-123,24,SM4007,C64898
"D11, D12, D15, D16, D19, D20, D23, D24, D27, D28, D3, D31, D32, D35, D36, D39, D4, D40, D43, D44, D47, D48, D7, D8",0402,24,RED LED,C397045
D2,D_SMA,1,SS54,C22452
F1,Fuseholder_2AG_5x15mm_Littelfuse_01110501Z,1,Fuse,C151075
J1,TerminalBlock_Phoenix_MKDS-1-2-3.81_1x02_P3.81mm_Horizontal,1,Terminal Block,C89123
"J2, J3",JST_SH_BM04B-SRSS-TB_1x04-1MP_P1.00mm_Vertical,2,JST-SH 01x04,C160390
"J4, J5, J6",PinSocket_2x08_P2.54mm_Vertical,3,Conn_02x08_Odd_Even,C30734
L1,L_Sunlord_SWPA6045S,1,68uH,C53663
R1,0603,1,6.8k,C23212
"R10, R11, R16, R17, R22, R23, R28, R29, R34, R35, R4, R40, R41, R46, R47, R5, R52, R53, R58, R59, R64, R65, R70, R71",0402,24,220R,C25091
"R12, R13, R18, R19, R24, R25, R30, R31, R36, R37, R42, R43, R48, R49, R54, R55, R6, R60, R61, R66, R67, R7, R72, R73",0402,24,5.1k,C25905
"R14, R15, R20, R21, R26, R27, R32, R33, R38, R39, R44, R45, R50, R51, R56, R57, R62, R63, R68, R69, R74, R75, R8, R9",0402,24,100k,C25741
"R2, R3",0402,2,100,C25076
R76,0805,1,0Ω,C17477
U1,Converter_DCDC_RECOM_R-78E-0.5_THT,1,R-78E5.0-1.0,C22371890
"U10, U11, U12, U13, U14, U15, U16, U17, U6, U7, U8, U9",SOIC-8_3.9x4.9mm_P1.27mm,12,AO4882,C477943
U2,SOT-23-6_Handsoldering,1,SN74LVC2G17,C10429
"U3, U4, U5",TSSOP-16_4.4x5mm_P0.65mm,3,74HC595,C273642

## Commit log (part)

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2026-05-06 Driver board done
2026-05-26 Further progress on the brain
